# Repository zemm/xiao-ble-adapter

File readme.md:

# XIAO BLE 10440 (AAA) adapter for Bastard Keyboard Dactyls

Wireless XIAO Bluetooth holder PCB for Bastard Keyboards TBK Mini and Skeletyl (not tested). Scylla should otherwise work too, but the power switch can't be operated.

Modified from the [original Elite-C-holder](https://github.com/Bastardkb/Elite-C-holder) by [Bastard Keyboards](https://bastardkb.com/), Quentin Lebastard and Alexander Krikun.

It encompasses an AAA battery holder for 3.7V 10440 Li-ion battery. As most of the 10440 Li-ions I found don't have protection circuits built in, I added a protection circuit for the battery based on the reference design of a [AP9101CAK6](https://www.mouser.fi/ProductDetail/621-AP9101CAK6BVTRG1) protection IC.

**I have no idea what I'm doing, so this is probably not safe and fine!**. Use at your own risk, or better yet, don't use at all. I claim no responsibility of any damage caused by this.

The original Elite C adapter supports Nice!nano and LiPO. Please consider using it instead.

The power switch is accessible through the open side of the TBK Mini and Skeletyl.

## Status

Initially tested as working.

## Firmware

[ZMK Module](https://github.com/zemm/zmk-config-bkd-xiao-ble).

## BOM & build info

[Schematic](xiao-ble-adapter-v0.1-schematic.pdf)

| Part              | Qty | Info    |
| ----------------- | --- | ------- |
| C 100n            | 2   | 0805    |
| R 330             | 2   | 0805    |
| R 2.7k            | 2   | 0805    |
| MCU               | 2   | I used Seeed Studio XIAO nRF52740, but nRF52840 probably works too.          |
| Battery holder    | 2   | [Keystone 2466 1xAAA](https://www.mouser.fi/ProductDetail/534-2466)          |
| Reset button      | 2   | Generic 4 pin SMD push button                                                |
| Power switch      | 2   | [Nidec CL-SB-12B-01T](https://www.mouser.fi/ProductDetail/229-CL-SB-12B-01T) |
| Protection IC     | 2   | SOT-23-6 AP9101CK6 variant. I used AP9101CAK6-BVTRG1 due to availability, but some other models had more suitable threshold values. |
| N-Channel MOSFET  | 4   | SOT-23 GSD. I used [SI2312CDS-T1-GE3](https://www.digikey.fi/fi/products/detail/vishay-siliconix/SI2312CDS-T1-GE3/2441583). |

As the XIAO is mounted flush with the adapter pcb, there are two through-holes for XIAO positive battery and reset connections. They are meant to be soldered from the connector to the plated side wall of the through-hole.

## Removed features

I made this for my specific use case with my TBK mini, not as universal solution. As the XIOA has much less pins than the Elite C based MCUs, the features were heavily cut to a minimum.

I also don't generally use or need the removed features in wireless builds because of missing support or battery drain, although they would make more sense here with the added capacity of the 10440 battery. Maybe in a future revision?

It would be possible to have more pins and therefore retain the features by using a shift register (ZMK supports this), but at least for this first version, I was in a hurry and did not bother.

- Removed audio socket (as ZMK and batteries are wireless only).
- Removed RGB support.
- Removed Trackball support.
- Removed handedness resistor.

## Future improvements

Things I'd like to change if doing it again.

- Find a toggle push button fitting through the unused audio socket hole to be used as the power switch.
- If still using the current slide power switch, swap it around so that "on" is facing away from you.
- Add RGB support either by dropping the row pin unused by TBK Mini and Skeletyl (dropping Scylla support) or by using a shift register for the matrix.
  - 10440 might have enough capacity for this to make some sense after all?
  - The leds have a minimum supply voltage of ~3.4V, how could that be handled?

# License

CERN Open Hardware Licence Version 2 - Weakly Reciprocal

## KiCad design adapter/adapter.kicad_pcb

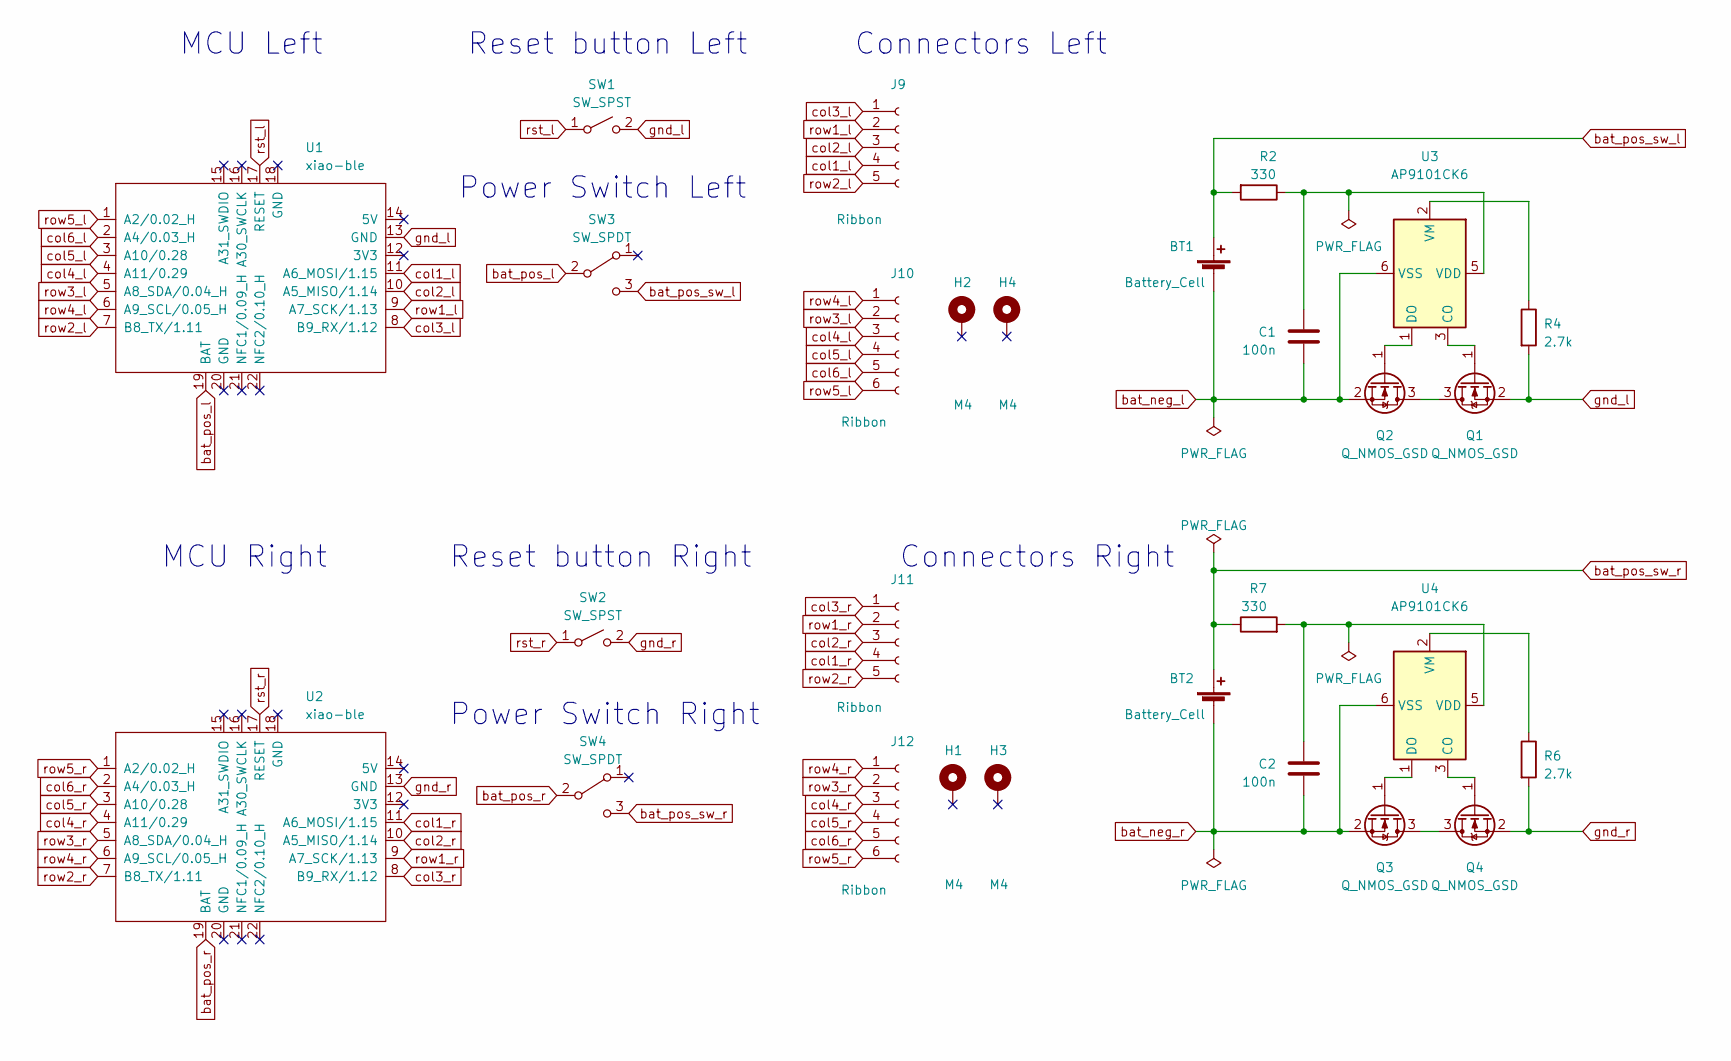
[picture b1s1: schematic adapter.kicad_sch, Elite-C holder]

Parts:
BT1, BT2: Battery_Cell; BatteryHolder_Keystone_2466_1xAAA
C1, C2: 100n; C_0805_2012Metric_Pad1.18x1.45mm_HandSolder
H1, H2, H3, H4: M4; MountingHole_4mm_Pad_thin
J9, J11: Ribbon; 5_PinHeader
J10, J12: Ribbon; 6_PinHeader
Q1, Q2, Q3, Q4: Q_NMOS_GSD; SOT-23
R2, R7: 330; R_0805_2012Metric_Pad1.20x1.40mm_HandSolder; JLCPCB BOM 1
R4, R6: 2.7k; R_0805_2012Metric_Pad1.20x1.40mm_HandSolder; JLCPCB BOM 1
SW1, SW2: SW_SPST; PushSwitch
SW3, SW4: SW_SPDT; CL-SB-12B-01T
U1, U2: xiao-ble; xiao-ble-smd-2-bogo-cutout
U3, U4: AP9101CK6; SOT-23-6

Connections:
unnamed: Q1.3 (D), Q2.3 (D)
unnamed: Q1.1 (G), U3.3 (CO)
unnamed: Q2.1 (G), U3.1 (DO)
unnamed: Q3.3 (D), Q4.3 (D)
unnamed: Q3.1 (G), U4.1 (DO)
unnamed: Q4.1 (G), U4.3 (CO)
unnamed: C1.1, R2.1, U3.5 (VDD)
unnamed: R4.1, U3.2 (VM)
unnamed: C2.1, R7.2, U4.5 (VDD)
unnamed: R6.1, U4.2 (VM)
bat_neg_l: BT1.2 (-), C1.2, Q2.2 (S), U3.6 (VSS)
bat_neg_r: BT2.2 (-), C2.2, Q3.2 (S), U4.6 (VSS)
bat_pos_l: SW3.2 (B), U1.19 (BAT)
bat_pos_r: SW4.2 (B), U2.19 (BAT)
bat_pos_sw_l: BT1.1 (+), R2.2, SW3.3 (C)
bat_pos_sw_r: BT2.1 (+), R7.1, SW4.3 (C)
col1_l: J9.4, U1.11 (A6_MOSI/1.15)
col1_r: J11.4, U2.11 (A6_MOSI/1.15)
col2_l: J9.3, U1.10 (A5_MISO/1.14)
col2_r: J11.3, U2.10 (A5_MISO/1.14)
col3_l: J9.1, U1.8 (B9_RX/1.12)
col3_r: J11.1, U2.8 (B9_RX/1.12)
col4_l: J10.3, U1.4 (A11/0.29)
col4_r: J12.3, U2.4 (A11/0.29)
col5_l: J10.4, U1.3 (A10/0.28)
col5_r: J12.4, U2.3 (A10/0.28)
col6_l: J10.5, U1.2 (A4/0.03_H)
col6_r: J12.5, U2.2 (A4/0.03_H)
gnd_l: Q1.2 (S), R4.2, SW1.2 (B), U1.13 (GND)
gnd_r: Q4.2 (S), R6.2, SW2.2 (B), U2.13 (GND)
row1_l: J9.2, U1.9 (A7_SCK/1.13)
row1_r: J11.2, U2.9 (A7_SCK/1.13)
row2_l: J9.5, U1.7 (B8_TX/1.11)
row2_r: J11.5, U2.7 (B8_TX/1.11)
row3_l: J10.2, U1.5 (A8_SDA/0.04_H)
row3_r: J12.2, U2.5 (A8_SDA/0.04_H)
row4_l: J10.1, U1.6 (A9_SCL/0.05_H)
row4_r: J12.1, U2.6 (A9_SCL/0.05_H)
row5_l: J10.6, U1.1 (A2/0.02_H)
row5_r: J12.6, U2.1 (A2/0.02_H)
rst_l: SW1.1 (A), U1.17 (RESET)
rst_r: SW2.1 (A), U2.17 (RESET)

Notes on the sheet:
Power Switch Right
Reset button Left
Power Switch Left
Connectors Left
Reset button Right
MCU Left
MCU Right
Connectors Right

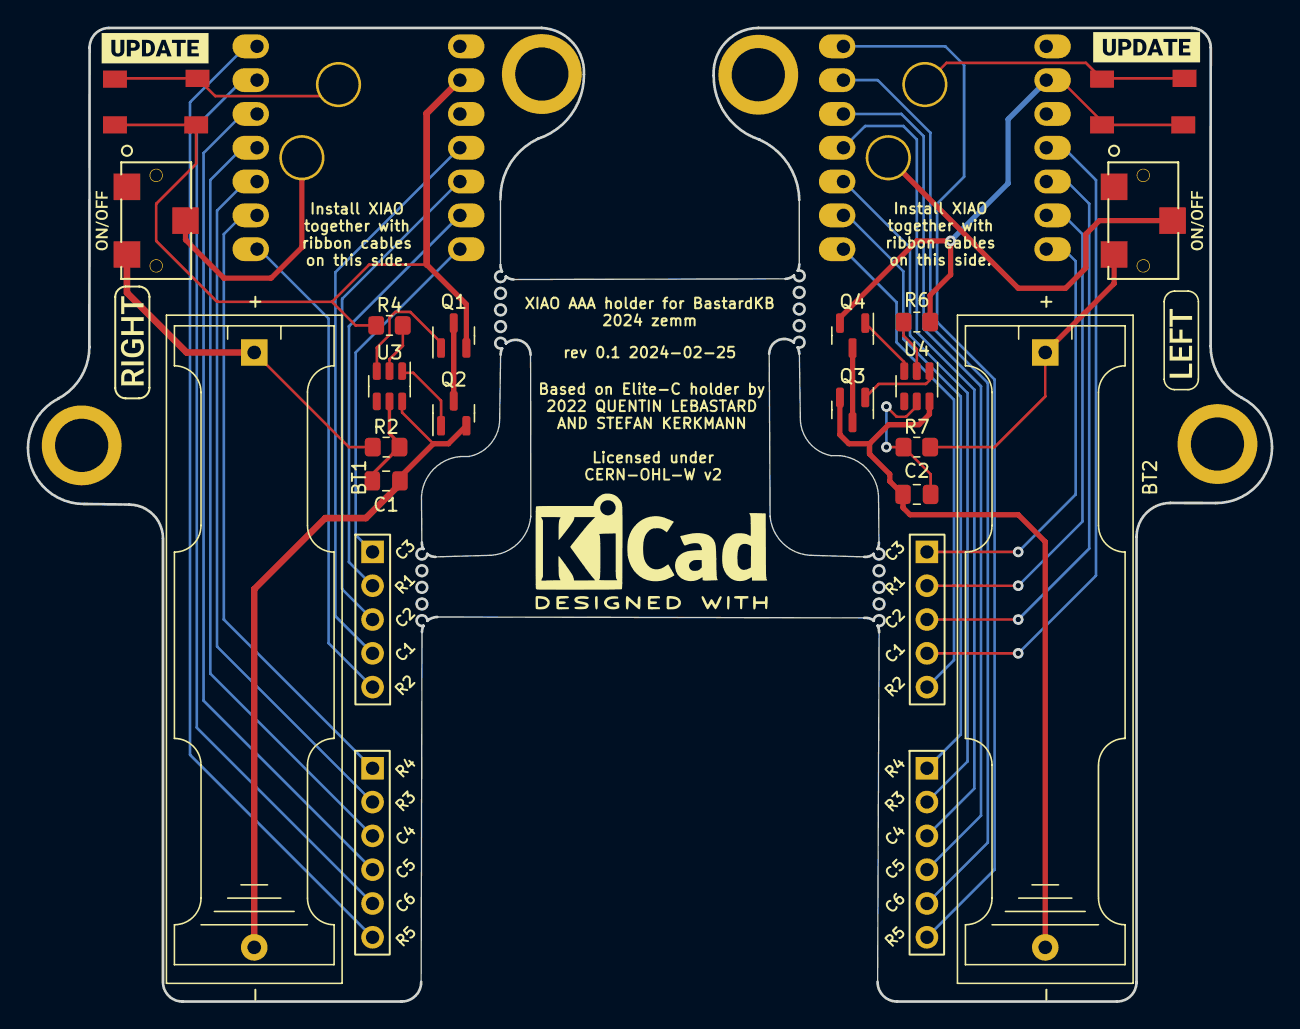
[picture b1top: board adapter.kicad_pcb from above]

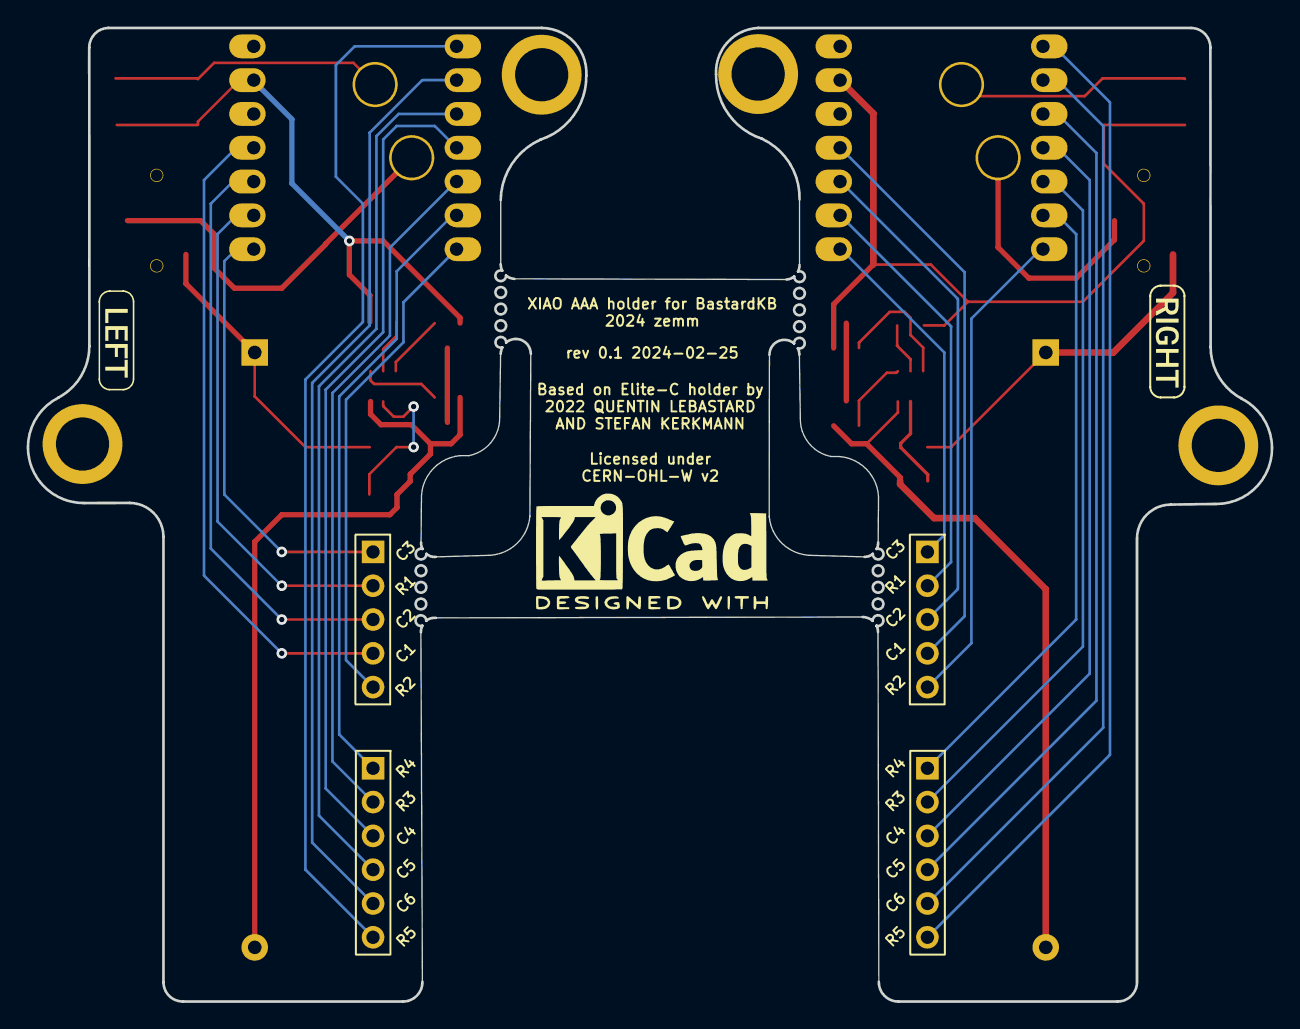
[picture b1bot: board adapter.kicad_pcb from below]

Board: 2 copper layers, 93.5 x 73.2 mm, 36 parts (2 on the bottom side), 42 nets.

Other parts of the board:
kibuzzard-61F01B61, kibuzzard-61F01B61#2: G***; kibuzzard-61F01B61
kibuzzard-61F01C84, kibuzzard-61F01C84#2: G***; kibuzzard-61F01C84
kibuzzard-620B8593, kibuzzard-620B8593#2: G***; kibuzzard-620B8593
kibuzzard-6208EFFE, kibuzzard-6208EFFE#2: G***; kibuzzard-6208EFFE

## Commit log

2024-02-26 Add initial untested XIAO BLE AAA adapter rev1 modified from Elite C holder
    This is not tested yet, and is not known to be working.
    Modified and based on https://github.com/Bastardkb/Elite-C-holder
2024-02-26 Docs: Make derivative work more explicit in the pcb text
    The previous version of the text in the PCB could have been misinterpreted so that the design of this PCB is by the creators of the original, which is not the case. This is an unnofficial derivative 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
2024-03-19 Fix the wrong license in the readme
    Confirm by the original author that the actual license is the CERN one, not the CC in the readme.
2024-03-19 Update the readme after initial testing of the real unit
    Seems to be working at least for the first few days...
2024-03-19 Fix the schematic info, add a schematic as pdf
    I like to read schematics by not having to download
    and open with KiCAD, so seems reasonable to do that
    with my project.
2024-03-21 Add firmware link and BOM

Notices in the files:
adapter/adapter.kicad_pcb:
Licensed under
CERN-OHL-W v2
adapter/adapter.kicad_sch:
Licensed under CERN-OHL-W v2
parts and their libraries:
Copyright 2016 Accelerated Designs. All rights reserved.
